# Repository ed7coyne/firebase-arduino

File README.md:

# FirebaseArduino

This repo contains a collection of samples and an Arduino library that show how to call the [Firebase](https://www.firebase.com/) API from the [ESP8266 Arduino core](https://github.com/esp8266/Arduino).

The Arduino library is [under heavy development](https://github.com/googlesamples/firebase-arduino/issues), **experimental**, **unversioned** and its API is **not stable**.

## Samples

- [FirebaseDemo](https://github.com/googlesamples/firebase-arduino/tree/master/examples/FirebaseDemo_ESP8266) - shows the FirebaseArduino API methods.
- [FirebaseRoom](https://github.com/googlesamples/firebase-arduino/tree/master/examples/FirebaseRoom_ESP8266) - shows how to push sensor data and trigger actuator from Firebase.
- [FirebaseStream](https://github.com/googlesamples/firebase-arduino/tree/master/examples/FirebaseStream_ESP8266) - shows the FirebaseArduino streaming API.
- [FirebaseNeoPixel](https://github.com/googlesamples/firebase-arduino/tree/master/examples/FirebaseNeoPixel_ESP8266) - shows how to control an array of LEDs from a Firebase web app. 

## Documentation

- [FirebaseArduino API Reference](http://firebase-arduino.readthedocs.io/)

## Disclaimer

*This is not an official Google product*.

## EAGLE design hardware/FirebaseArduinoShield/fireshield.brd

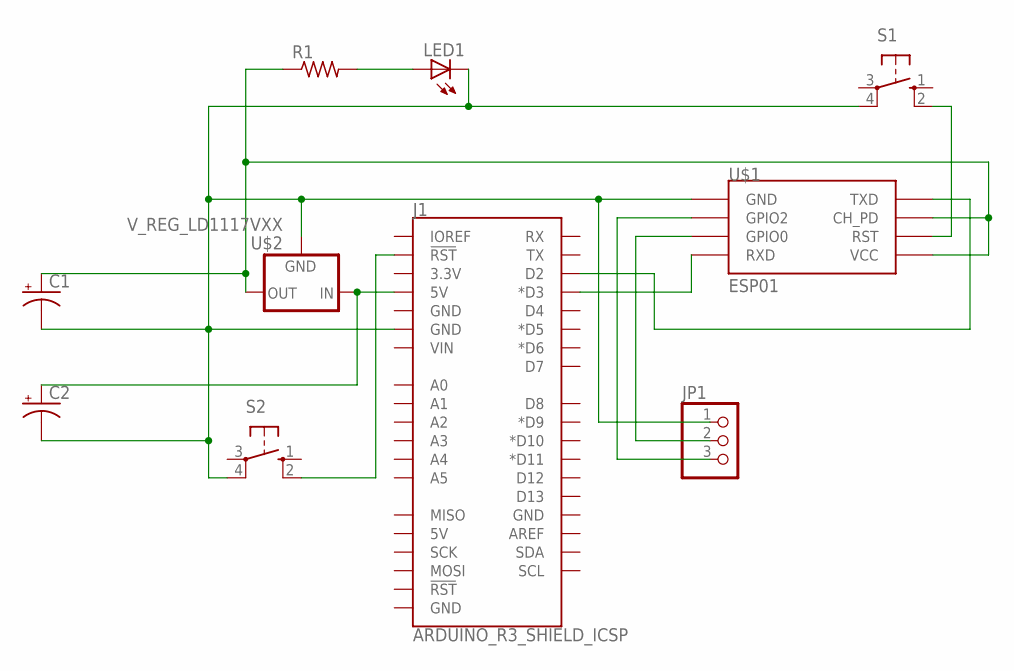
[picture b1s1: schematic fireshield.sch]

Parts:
C1, C2: 10UF-25V-20%(PTH)KIT; CPOL-RADIAL-10UF-25V-KIT
J1: ARDUINO_R3_SHIELD_ICSP; UNO_R3_SHIELD_ICSP
JP1: PINHD-1X3; 1X03
LED1: LED3MM
R1: R-US_0207/10; 0207/10
S1, S2: 10-XX; B3F-10XX
U$1: ESP01
U$2: V_REG_LD1117VXX; 78XXL

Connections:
unnamed: C1.2 (-), C2.2 (-), J1.GND@1 (GND), JP1.1, LED1.K (C), S1.4 (P1), S2.4 (P1), U$1.GND, U$2.IN (GND)
unnamed: J1.D3 (*D3), U$1.RX (RXD)
unnamed: C2.1 (+), J1.5V, U$2.OUT (IN)
unnamed: C1.1 (+), R1.1, U$1.CH_PD, U$1.VCC, U$2.GND (OUT)
unnamed: J1.D2, U$1.TX (TXD)
unnamed: S1.2 (S1), U$1.RST
unnamed: LED1.A, R1.2
unnamed: J1.RES (!RST!), S2.2 (S1)
unnamed: JP1.3, U$1.GPIO2
unnamed: JP1.2, U$1.GPIO0

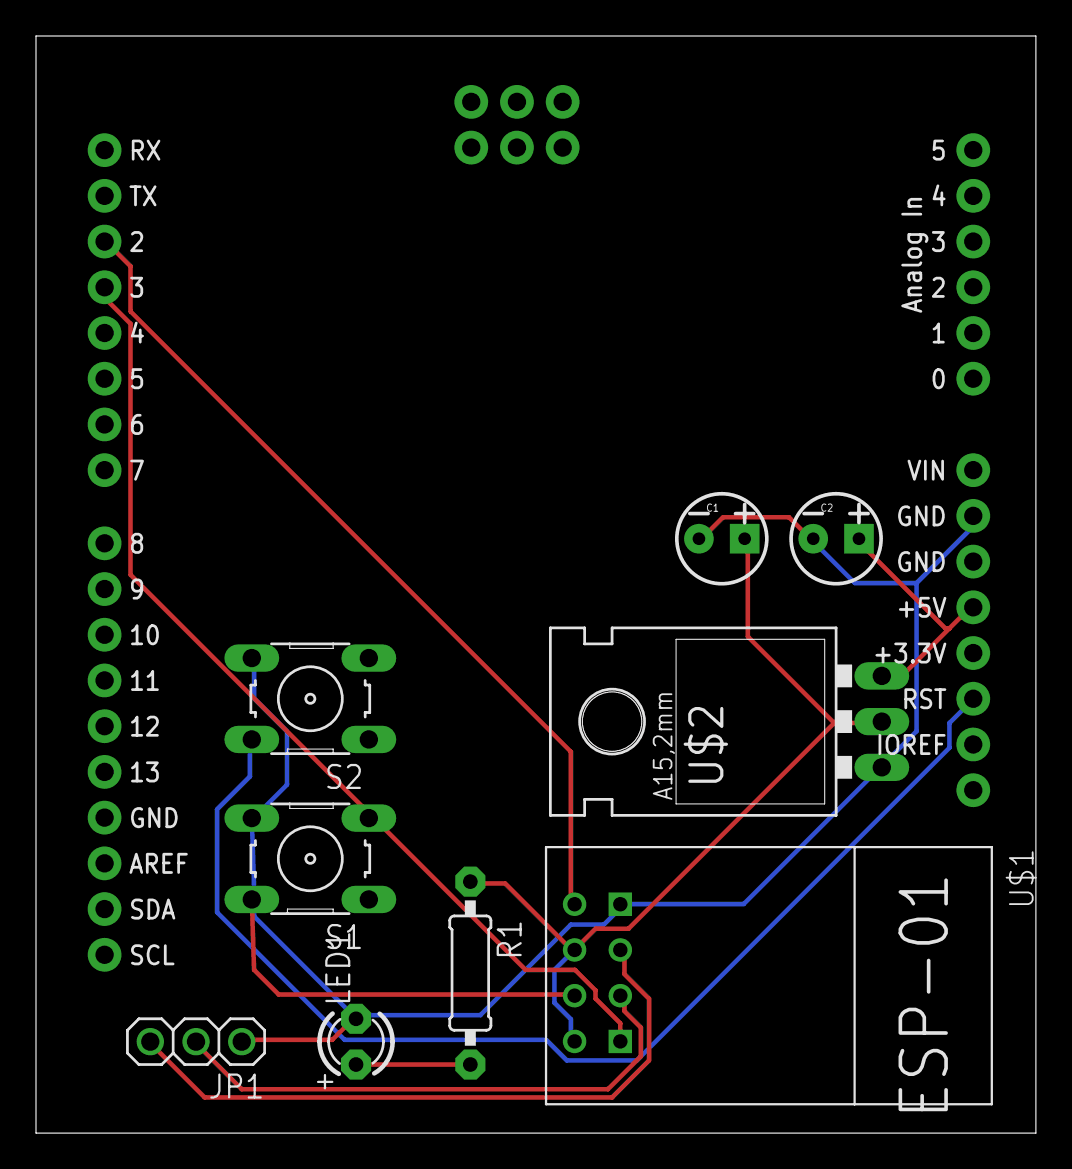
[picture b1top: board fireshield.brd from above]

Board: 2 copper layers, 55.5 x 61.0 mm, 10 parts (0 on the bottom side), 10 nets.

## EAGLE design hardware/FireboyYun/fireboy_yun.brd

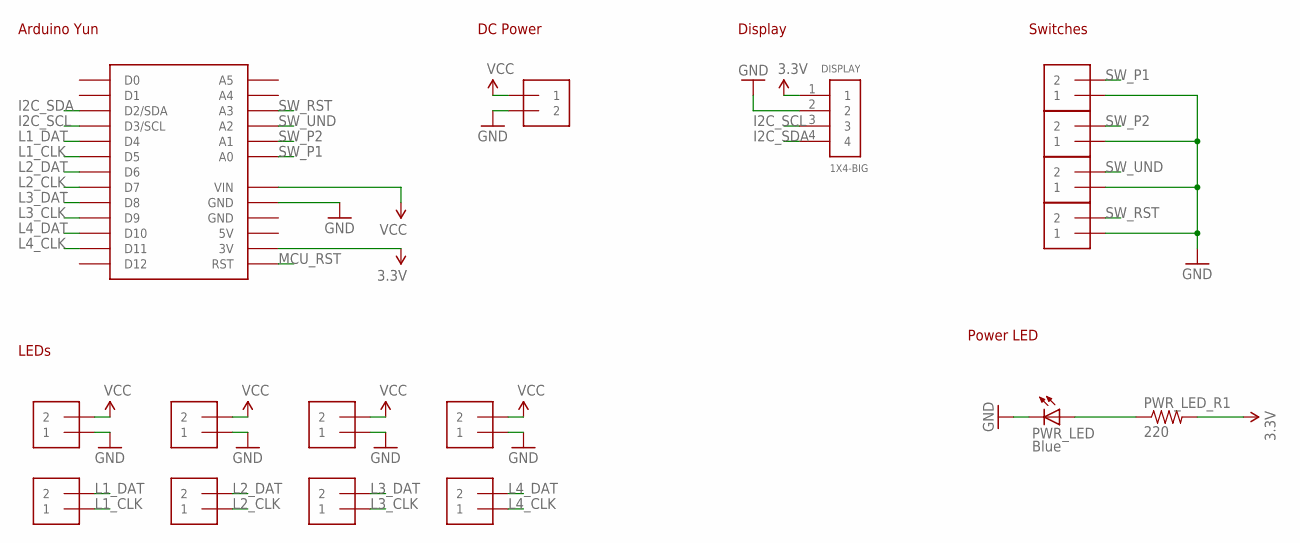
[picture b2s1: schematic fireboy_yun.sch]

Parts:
DC_5V_8A: 1X2-3.5MM
DISPLAY: 1X4-BIG; 1X04-BIG
L1_IO, L1_PWR, L2_IO, L2_PWR, L3_IO, L3_PWR, L4_IO, L4_PWR: 1X2-3.5MM
PWR_LED: Blue; LED3MM
PWR_LED_R1: 220; AXIAL-0.3
SW_P1, SW_P2: 1X2-3.5MM
SW_RST: 1X2-3.5MM
SW_UND: 1X2-3.5MM
YUN: YUN_MINI_SHIELD-BPLACE; YUN_MINI_SHIELD

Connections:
3.3V: DISPLAY.1, PWR_LED_R1.P$2 (2), YUN.3V
5V: YUN.5V
GND: DC_5V_8A.2, DISPLAY.2, L1_PWR.1, L2_PWR.1, L3_PWR.1, L4_PWR.1, PWR_LED.K (C), SW_P1.1, SW_P2.1, SW_RST.1, SW_UND.1, YUN.GND1 (GND), YUN.GND2 (GND)
I2C_SCL: DISPLAY.3, YUN.D3 (D3/SCL)
I2C_SDA: DISPLAY.4, YUN.D2 (D2/SDA)
L1_CLK: L1_IO.1, YUN.D5
L1_DAT: L1_IO.2, YUN.D4
L2_CLK: L2_IO.1, YUN.D7
L2_DAT: L2_IO.2, YUN.D6
L3_CLK: L3_IO.1, YUN.D9
L3_DAT: L3_IO.2, YUN.D8
L4_CLK: L4_IO.1, YUN.D11
L4_DAT: L4_IO.2, YUN.D10
MCU_RST: YUN.RESET (RST)
PWR_LED_R: PWR_LED.A, PWR_LED_R1.P$1 (1)
SW_P1: SW_P1.2, YUN.A0
SW_P2: SW_P2.2, YUN.A1
SW_RST: SW_RST.2, YUN.A3
SW_UND: SW_UND.2, YUN.A2
VCC: DC_5V_8A.1, L1_PWR.2, L2_PWR.2, L3_PWR.2, L4_PWR.2, YUN.VIN

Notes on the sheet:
Arduino Yun
LEDs
DC Power
Display
Switches
Power LED

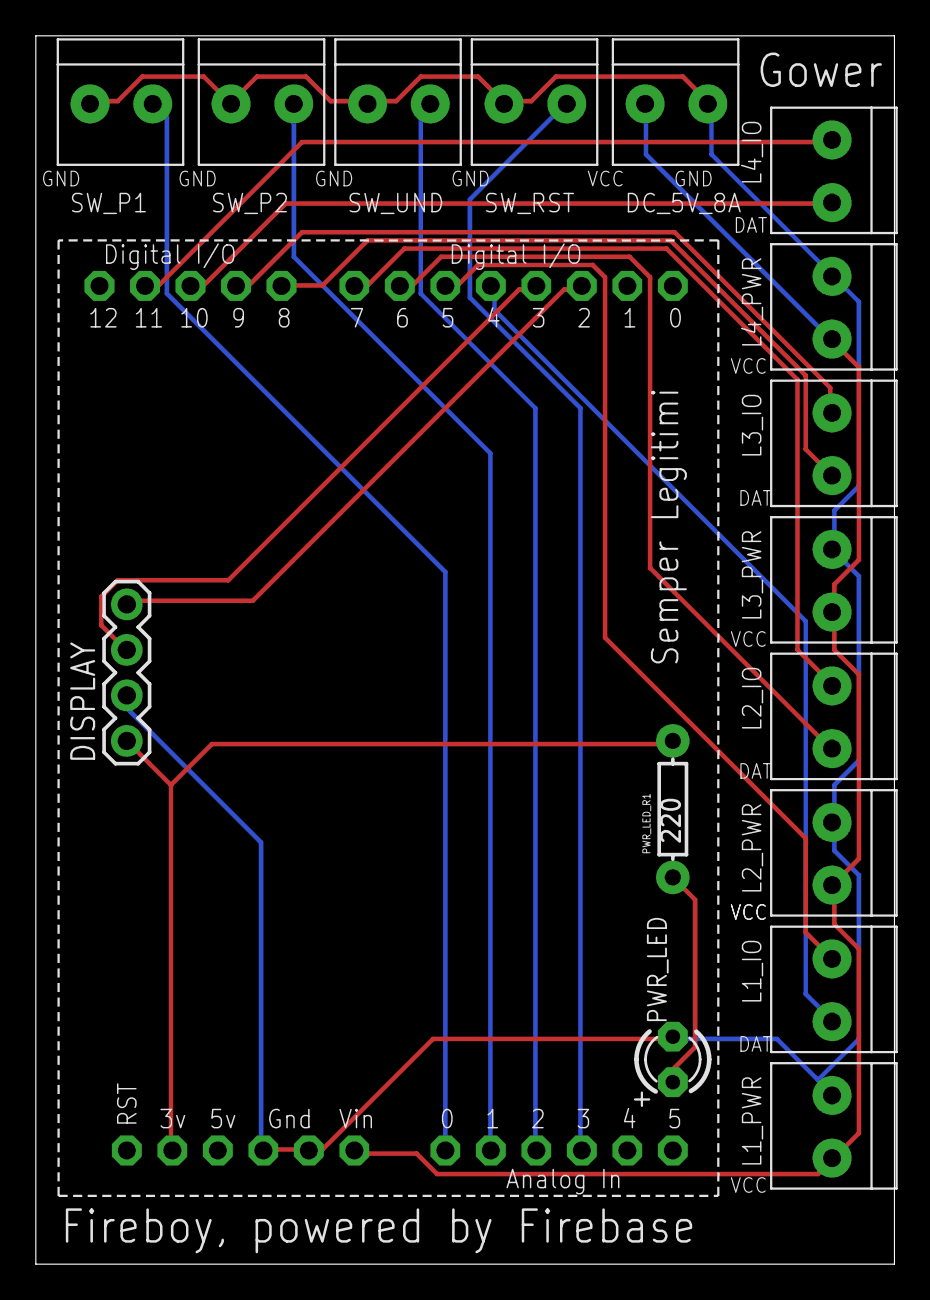
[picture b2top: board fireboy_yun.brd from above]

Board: 2 copper layers, 47.9 x 68.6 mm, 17 parts (0 on the bottom side), 18 nets.

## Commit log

2016-08-26 Added messaging protocol, initial code no tests yet, probably doesn
2016-08-26 Added msg protocol, intial version, no tests, probably doesnt compile
2016-08-26 minor tweaks

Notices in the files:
parts and their libraries:
SparkFun-Boards: Licensing: Creative Commons ShareAlike 4.0 International - https://creativecommons.org/licenses/by-sa/4.0
